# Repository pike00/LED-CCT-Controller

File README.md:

# LED CCT Controller
This repository holds design files and code related to my ESP32 based LED CCT Controlled.

## Problem Statement
Light is an important part of any living situation. One factor that is often overlooked is [Color Temperature](https://www.westinghouselighting.com/color-temperature.aspx), measured in Kelvin. A typical range is from 2700K-5000K, with lower numbers being redder and higher numbers being 'brighter' and bluer. 

I appreciate the role that [f.lux](https://justgetflux.com/) has on my computer screen color, and I have attempted to emulate similar room lighting using a [Phillips Wake up Light](https://www.usa.philips.com/c-p/HF3471_60/wake-up-light). However, I would like to have control over the lights being on/off and their color temperature throughout the day automatically. 

## The plan
To accomplish this, I set out to design a system that could be incorporated in my Home Assistant Setup, so that I can easily integrate it into my location based automations and even incorporate my digital calendar (i.e. if I am working at night, I want the color temperature to mirror my schedule). 

I wanted to combine an ESP32 using [ESPHome (Specifically the Cool White + Warm White Light platform)](https://esphome.io/components/light/cwww.html), combined with a white tunable ("CCT") LED strip that I can customize and place around the house. 

## Parts

### ESP32
For this project, I have been using an [DOIT ESP32 DEVKIT v1](https://www.mischianti.org/wp-content/uploads/2021/03/ESP32-DOIT-DEV-KIT-v1-pinout-mischianti-1024x501.jpg) as the base. 

For future iterations, I may plan to just use the ESP32 module (i.e. without the development board), e.g. [ESP-WROOM-32](https://www.digikey.com/catalog/en/partgroup/esp-wroom-32/75395), but this will require me to be able to solder/have on hand many SMD Resistors and capacitors. 

### LED strips
For the first iteration, I am using the [5m Tunable White LED Strip Lights, 12V](https://www.superbrightleds.com/moreinfo/flexible-led-strip-lights/5m-tunable-white-led-strip-light-color-changing-led-tape-light-12v24v-ip20/5497/12019/) from [superbrightleds.com](superbrightleds.com). It is definitely a bit on the pricey side, and I plan to source cheaper parts from aliexpress.com, but I wanted to have a strip that I could rely on to work to minimize troubleshooting steps. 

### Power Supply
I chose 12V LED strips intentionally (over 5V LEDs that are available) as I want to be able to power long runs of LEDs without significant voltage drop/heat dissipation concerns. It also allows me to buy a slightly cheaper power supply (fewer amps required). The LED strip above has a rating of 13.8 Watts/meter. As I bought 5 meters of LEDs, this works out to 5.75 amps of current at max load. 

I am only planning on (at least initially) using the LED strips for a maximum of 2-3 feet, for 1 amp. With that in mind, I picked up a 12V, 1 amp DC power supply. 

#### Stepping down to 3.3V

The ESP32 runs on 3.3V, however. I could not be bothered to design an include a switching buck converter, so I opted to include a pre-made [3.3V output, up to 21V input Buck converter](https://www.adafruit.com/product/4683) from adafruit that I can include with a 4 pin header. 

### Transistors

When choosing a transister, I went with one that can switch a high current (at least 1 amp) of 12V, and quick on/off time (so I can run PWM signals from the ESP32 at at least 1kHz). Based on some quick googling, I've narrowed down to two: 

- [IRLB8721 (N-channel power MOSFET, TO-220)](https://octopart.com/irlb8721pbf-infineon-65874927?r=sp). Can carry up to at least 15A without a heat sink (Rds . Purchased from [Adafruit](https://www.adafruit.com/product/355). Threshold voltage Max of 2.35V (< 3.3 V as required from ESP32). This is *confirmed* to work. 
- [FQP30N06 (N-Channel MOSFET, TO-220)](https://octopart.com/fqp30n06-onsemi-84328004?r=sp). Looks very similar to IRLB8721. Gate threshold voltage max of 4.0, may not work. **Unconfirmed**.

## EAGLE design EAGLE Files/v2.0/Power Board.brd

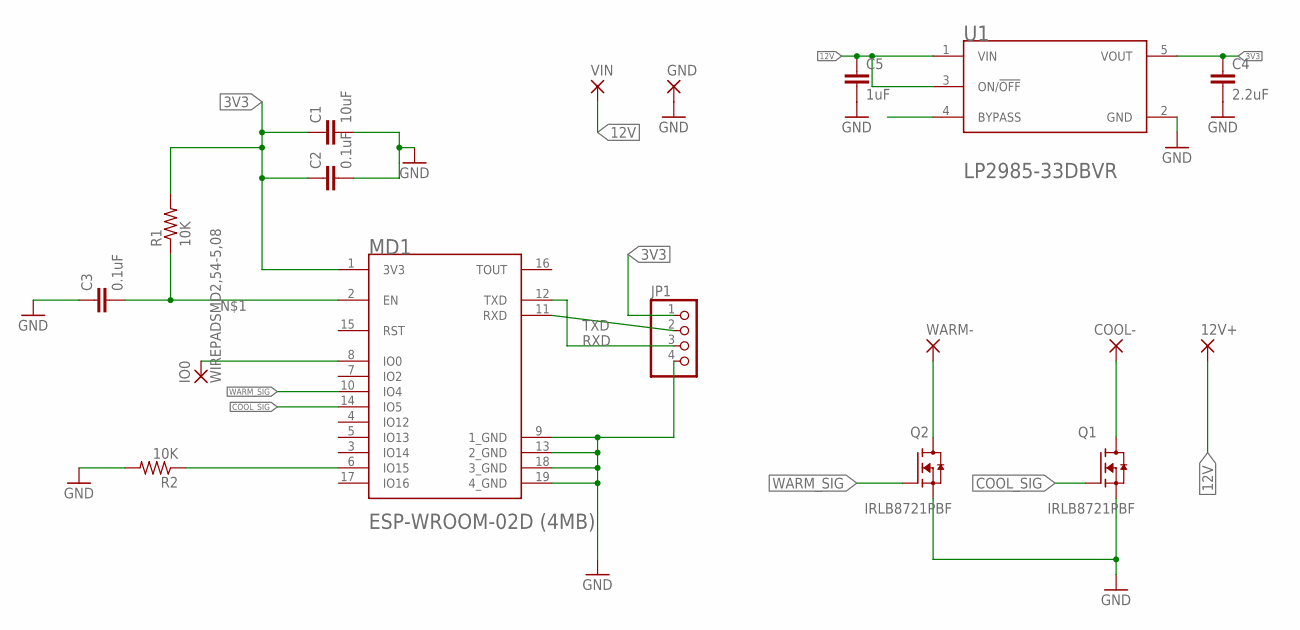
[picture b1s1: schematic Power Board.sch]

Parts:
12V+: WIREPADSMD5-2,5; 5-2,5
C1: 10uF; C1206
C2, C3: 0.1uF; C1206
C4: 2.2uF; C1206
C5: 1uF; C1206
COOL-: WIREPADSMD5-2,5; 5-2,5
GND: WIREPADSMD5-2,5; 5-2,5
IO0: WIREPADSMD2,54-5,08; SMD2,54-5,08
JP1: PINHD-1X4; 1X04
MD1: ESPRESSIF_SYSTEMS_ESP-WROOM-02D_4MBESPRESSIF_SYST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; ESPRESSIF_SYSTEMS_ESP-WROOM-02D_4MB_0
Q1, Q2: IRLB8721PBF; TO254P1067X483X2057-3
R1, R2: 10K; R1206
U1: TEXAS_INSTRUMENTS_LP2985-33DBVRTEXAS_INSTRUMENTS_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; TEXAS_INSTRUMENTS_LP2985-33DBVR_0
VIN: WIREPADSMD5-2,5; 5-2,5
WARM-: WIREPADSMD5-2,5; 5-2,5

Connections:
3V3: C1.1, C2.1, C4.1, JP1.1, MD1.1 (3V3), R1.2, U1.5 (VOUT)
12V: 12V+.1, C5.1, U1.1 (VIN), U1.3 (ON/!OFF!), VIN.1
COOL-: COOL-.1, Q1.2 (D)
COOL_SIG: MD1.14 (IO5), Q1.1 (G)
GND: C1.2, C2.2, C3.1, C4.2, C5.2, GND.1, JP1.4, MD1.9 (1_GND), MD1.13 (2_GND), MD1.18 (3_GND), MD1.19 (4_GND), Q1.3 (S), Q2.3 (S), R2.2, U1.2 (GND)
IO0: IO0.1, MD1.8 (IO0)
unnamed: C3.2, MD1.2 (EN), R1.1
unnamed: MD1.6 (IO15), R2.1
RXD: JP1.2, MD1.11 (RXD)
TXD: JP1.3, MD1.12 (TXD)
WARM-: Q2.2 (D), WARM-.1
WARM_SIG: MD1.10 (IO4), Q2.1 (G)

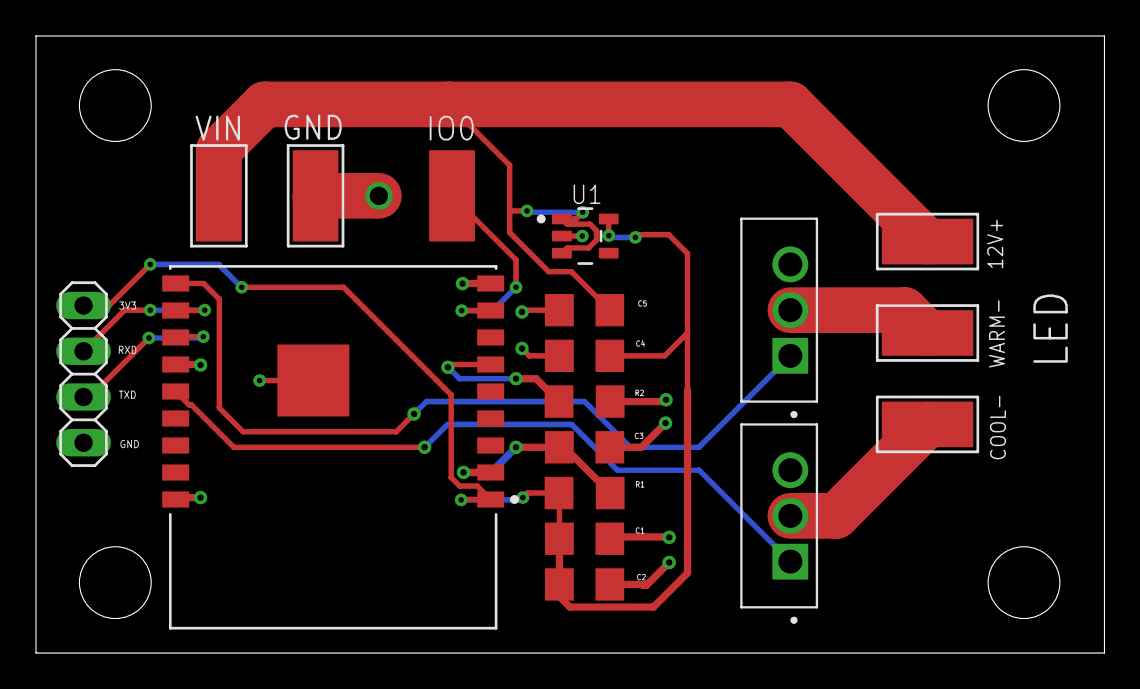
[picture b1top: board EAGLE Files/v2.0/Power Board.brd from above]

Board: 2 copper layers, 59.4 x 34.3 mm, 18 parts (0 on the bottom side), 12 nets.

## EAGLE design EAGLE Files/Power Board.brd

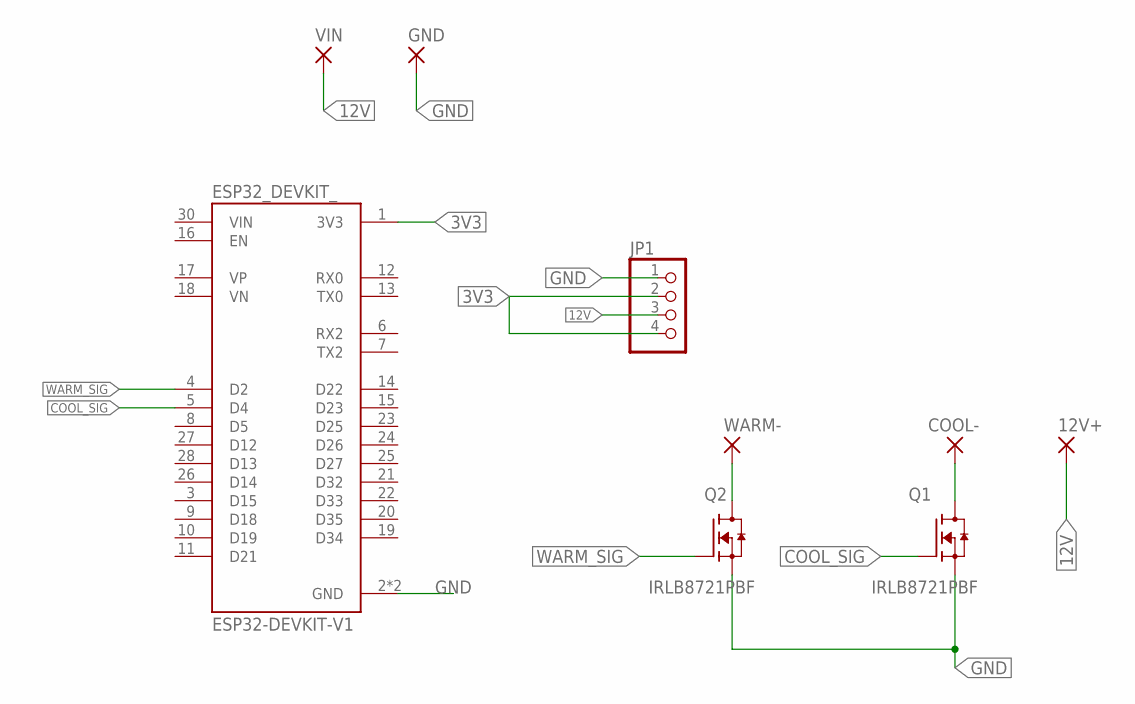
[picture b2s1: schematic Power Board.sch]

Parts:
12V+: WIREPADSMD5-2,5; 5-2,5
COOL-: WIREPADSMD5-2,5; 5-2,5
ESP32_DEVKIT_: ESP32-DEVKIT-V1; MODULE_ESP32_DEVKIT_V1
GND: WIREPADSMD5-2,5; 5-2,5
JP1: PINHD-1X4; 1X04
Q1, Q2: IRLB8721PBF; TO254P1067X483X2057-3
VIN: WIREPADSMD5-2,5; 5-2,5
WARM-: WIREPADSMD5-2,5; 5-2,5

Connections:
3V3: ESP32_DEVKIT_.1 (3V3), JP1.2, JP1.4
12V: 12V+.1, JP1.3, VIN.1
COOL-: COOL-.1, Q1.2 (D)
COOL_SIG: ESP32_DEVKIT_.5 (D4), Q1.1 (G)
GND: ESP32_DEVKIT_.2 (GND), ESP32_DEVKIT_.29 (GND), GND.1, JP1.1, Q1.3 (S), Q2.3 (S)
WARM-: Q2.2 (D), WARM-.1
WARM_SIG: ESP32_DEVKIT_.4 (D2), Q2.1 (G)

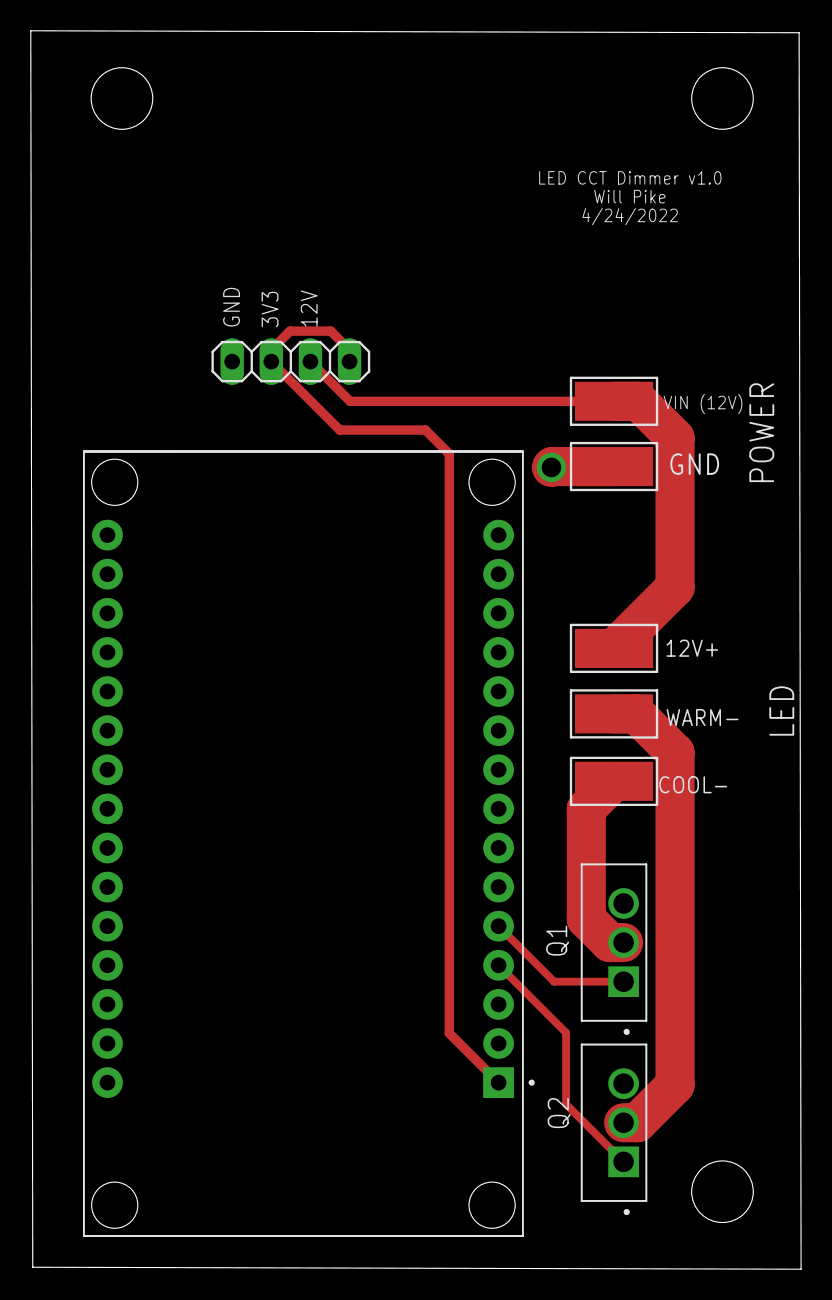
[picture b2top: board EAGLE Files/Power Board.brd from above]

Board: 2 copper layers, 50.0 x 80.4 mm, 9 parts (0 on the bottom side), 7 nets.

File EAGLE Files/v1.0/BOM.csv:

Part,Value,Device,Package,Description,AVAILABILITY,DESCRIPTION,MF,MP,PACKAGE,POPULARITY,PRICE,PURCHASE-URL
12V+,"WIREPADSMD5-2,5","WIREPADSMD5-2,5","5-2,5",Wire PAD connect wire on PCB,,,,,,3,,
COOL-,"WIREPADSMD5-2,5","WIREPADSMD5-2,5","5-2,5",Wire PAD connect wire on PCB,,,,,,3,,
ESP32_DEVKIT_,ESP32-DEVKIT-V1,ESP32-DEVKIT-V1,MODULE_ESP32_DEVKIT_V1,"Dual core, Wi-Fi: 2.4 GHz up to 150 Mbits/s,BLE (Bluetooth Low Energy) and legacy Bluetooth, 32 bits, Up to 240 MHz    Check availability",Not in stock," Dual core, Wi-Fi: 2.4 GHz up to 150 Mbits/s,BLE (Bluetooth Low Energy) and legacy Bluetooth, 32 bits, Up to 240 MHz ",Do it,ESP32-DEVKIT-V1,None,,None,
GND,"WIREPADSMD5-2,5","WIREPADSMD5-2,5","5-2,5",Wire PAD connect wire on PCB,,,,,,3,,
JP1,,PINHD-1X4,1X04,PIN HEADER,,,,,,91,,
Q1,IRLB8721PBF,IRLB8721PBF,TO254P1067X483X2057-3,Single N-Channel 30 V 8.7 mOhm 13 nC HEXFET® Power Mosfet - TO-220-3 Check availability,In Stock, Very Low RDS(on) at 4.5V VGS | Ultra-Low Gate Impedance | Fully Characterized Avalanche Voltage and Current | Lead-Free ,Infineon Technologies,IRLB8721PBF,TO-220 Infineon,,None,https://pricing.snapeda.com/search/part/IRLB8721PBF/?ref=eda
Q2,IRLB8721PBF,IRLB8721PBF,TO254P1067X483X2057-3,Single N-Channel 30 V 8.7 mOhm 13 nC HEXFET® Power Mosfet - TO-220-3 Check availability,In Stock, Very Low RDS(on) at 4.5V VGS | Ultra-Low Gate Impedance | Fully Characterized Avalanche Voltage and Current | Lead-Free ,Infineon Technologies,IRLB8721PBF,TO-220 Infineon,,None,https://pricing.snapeda.com/search/part/IRLB8721PBF/?ref=eda
VIN,"WIREPADSMD5-2,5","WIREPADSMD5-2,5","5-2,5",Wire PAD connect wire on PCB,,,,,,3,,
WARM-,"WIREPADSMD5-2,5","WIREPADSMD5-2,5","5-2,5",Wire PAD connect wire on PCB,,,,,,3,,

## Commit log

2022-05-10 Added info about Transistor
2022-05-10 Uploaded EAGLE Files v1.0
2022-05-10 Reorganized into version numbers
2023-03-30 Updated files
